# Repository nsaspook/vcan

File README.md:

# vcan

pic32mkmc Viision can motor tester

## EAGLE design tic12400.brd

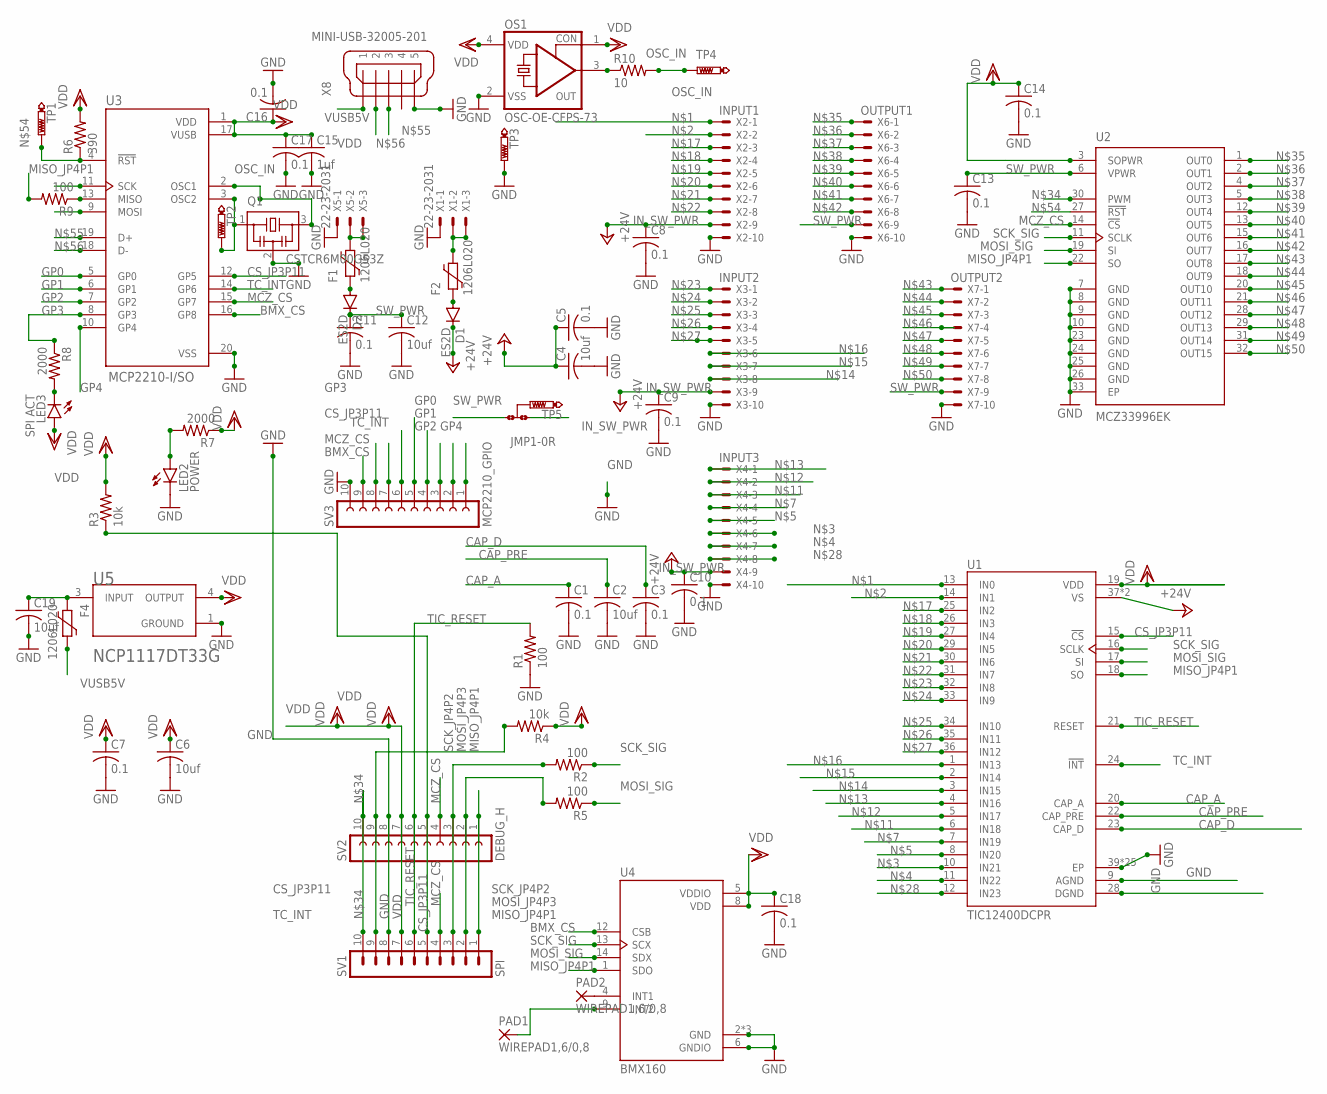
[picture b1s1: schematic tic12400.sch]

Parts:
C1, C3, C5, C7, C8, C9, C10, C11, C13, C14, C16, C17, C18: 0.1; C0805
C2, C4, C6, C12, C19: 10uf; C0805
C15: 1uf; C0805
D1, D2: ES2D; SMB
F1, F2, F4: 1206L020; 1206L
JMP1: +24_CONNECT; A0R-JMP
LED2: POWER; CHIP-LED0805
LED3: SPI ACT; CHIP-LED0805
OS1: OSC-OE-CFPS-73; 7.2X5.2-4-PAD
PAD1, PAD2: WIREPAD1,6/0,8; 1,6/0,8
Q1: CSTCR6M00G53Z; CSTCR6M
R1, R2, R5, R9: 100; R0805
R3, R4: 10k; R0805
R6: 390; R0805
R7, R8: 2000; R0805
R10: 10; R0805
SV1: SPI; MA10-1
SV2: DEBUG_H; FE10
SV3: MCP2210_GPIO; FE10
TP1, TP2, TP3, TP4, TP5: PTR1B1,27; B1,27
U1: TIC12400DCPR; SOP50P640X120-38N
U2: MCZ33996EK; SOP65P1030X265-33N
U3: MCP2210-I/SO; SOP65P780X200-20N
U4: BMX160; PQFN50P250X300X100-14N
U5: ON_SEMICONDUCTOR_NCP1117DT33GON_SEMICONDUCTOR_NCP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; ON_SEMICONDUCTOR_NCP1117DT33G_0
X1, X5: 22-23-2031
X2: INPUT1; KK-156-10
X3: INPUT2; KK-156-10
X4: INPUT3; KK-156-10
X6: OUTPUT1; KK-156-10
X7: OUTPUT2; KK-156-10
X8: MINI-USB-32005-201; 32005-201

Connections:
BMX_CS: SV3.9, U3.16 (GP8), U4.12 (CSB)
CAP_A: C1.1, U1.20 (CAP_A)
CAP_D: C3.1, U1.23 (CAP_D)
CAP_PRE: C2.1, U1.22 (CAP_PRE)
CS_JP3P11: R3.1, SV1.5, SV2.5, SV3.6, U1.15 (!CS), U3.12 (GP5)
GND: C1.2, C2.2, C3.2, C4.2, C5.2, C6.2, C7.2, C8.2, C9.2, C10.2, C11.2, C12.2, C13.2, C14.2, C15.2, C16.2, C17.2, C18.2, C19.2, LED2.C, OS1.2 (VSS), Q1.2, R1.1, SV1.8, SV2.8, SV3.10, TP3.TP, U1.9 (AGND), U1.28 (DGND), U1.39 (EP), U1.40 (EP), U1.41 (EP), U1.42 (EP), U1.43 (EP), U1.44 (EP), U1.45 (EP), U1.46 (EP), U1.47 (EP), U1.48 (EP), U1.49 (EP), U1.50 (EP), U1.51 (EP), U1.52 (EP), U1.53 (EP), U1.54 (EP), U1.55 (EP), U1.56 (EP), U1.57 (EP), U1.58 (EP), U1.59 (EP), U1.60 (EP), U1.61 (EP), U1.62 (EP), U1.63 (EP), U2.7 (GND), U2.8 (GND), U2.9 (GND), U2.10 (GND), U2.23 (GND), U2.24 (GND), U2.25 (GND), U2.26 (GND), U2.33 (EP), U3.20 (VSS), U4.2 (GND), U4.3 (GND), U4.6 (GNDIO), U4.7 (GND), U5.1 (GROUND), X1.1, X2.10, X3.10, X4.10, X5.1, X6.10, X7.10, X8.5; also elsewhere on the board
GP0: SV3.1, U3.5 (GP0)
GP1: SV3.2, U3.6 (GP1)
GP2: SV3.3, U3.7 (GP2)
GP3: R8.1, SV3.4, U3.8 (GP3)
GP4: SV3.5, U3.10 (GP4)
IN_SW_PWR: C4.1, C5.1, C8.1, C9.1, C10.1, D1.C, JMP1.3, U1.37 (VS), U1.38 (VS), X2.9, X3.9, X4.9
MCZ_CS: SV1.4, SV2.4, SV3.8, U2.14 (!CS), U3.15 (GP7)
MISO_JP4P1: R9.2, SV1.1, SV2.1, U1.18 (SO), U2.22 (SO), U4.1 (SDO)
MOSI_JP4P3: R5.2, SV1.2, SV2.2
MOSI_SIG: R5.1, U1.17 (SI), U2.19 (SI), U3.9 (MOSI), U4.14 (SDX)
unnamed: U1.13 (IN0), X2.1
unnamed: U1.14 (IN1), X2.2
unnamed: U1.10 (IN21), X4.6
unnamed: U1.11 (IN22), X4.7
unnamed: U1.8 (IN20), X4.5
unnamed: U1.7 (IN19), X4.4
unnamed: U1.6 (IN18), X4.3
unnamed: U1.5 (IN17), X4.2
unnamed: U1.4 (IN16), X4.1
unnamed: U1.3 (IN15), X3.8
unnamed: U1.2 (IN14), X3.7
unnamed: U1.1 (IN13), X3.6
unnamed: U1.25 (IN2), X2.3
unnamed: U1.26 (IN3), X2.4
unnamed: U1.27 (IN4), X2.5
unnamed: U1.29 (IN5), X2.6
unnamed: U1.30 (IN6), X2.7
unnamed: U1.31 (IN7), X2.8
unnamed: U1.32 (IN8), X3.1
unnamed: U1.33 (IN9), X3.2
unnamed: U1.34 (IN10), X3.3
unnamed: U1.35 (IN11), X3.4
unnamed: U1.36 (IN12), X3.5
unnamed: U1.12 (IN23), X4.8
unnamed: F2.1, X1.2, X1.3
unnamed: D2.A, F1.2
unnamed: F1.1, X5.2, X5.3
unnamed: SV1.10, SV2.10, U2.30 (PWM)
unnamed: U2.1 (OUT0), X6.1
unnamed: U2.2 (OUT1), X6.2
unnamed: U2.4 (OUT2), X6.3
unnamed: U2.5 (OUT3), X6.4
unnamed: U2.12 (OUT4), X6.5
unnamed: U2.13 (OUT5), X6.6
unnamed: U2.15 (OUT6), X6.7
unnamed: U2.16 (OUT7), X6.8
unnamed: U2.17 (OUT8), X7.1
unnamed: U2.18 (OUT9), X7.2
unnamed: U2.20 (OUT10), X7.3
unnamed: U2.21 (OUT11), X7.4
unnamed: U2.28 (OUT12), X7.5
unnamed: U2.29 (OUT13), X7.6
unnamed: U2.31 (OUT14), X7.7
unnamed: U2.32 (OUT15), X7.8
unnamed: D1.A, F2.2
unnamed: Q1.1, TP2.TP, U3.3 (OSC2)
unnamed: R6.1, TP1.TP, U2.27 (!RST), U3.4 (!RST)
unnamed: U3.19 (D+), X8.3
unnamed: U3.18 (D-), X8.2
unnamed: LED2.A, R7.2
unnamed: LED3.C, R8.2
unnamed: R9.1, U3.13 (MISO)
unnamed: OS1.3 (OUT), R10.1
unnamed: JMP1.2, TP5.TP
unnamed: PAD2.1, U4.4 (INT1)
unnamed: PAD1.1, U4.9 (INT2)
OSC_IN: Q1.3, R10.2, TP4.TP, U3.2 (OSC1)
SCK_JP4P2: R2.2, SV1.3, SV2.3
SCK_SIG: R2.1, U1.16 (SCLK), U2.11 (SCLK), U3.11 (SCK), U4.13 (SCX)
SW_PWR: C11.1, C12.1, C13.1, D2.C, JMP1.1, U2.6 (VPWR), X6.9, X7.9
TC_INT: R4.2, SV1.9, SV2.9, SV3.7, U1.24 (!INT), U3.14 (GP6)
TIC_RESET: R1.2, SV1.6, SV2.6, U1.21 (RESET)
USB5V_FUSE: C19.1, F4.2, U5.3 (INPUT); also elsewhere on the board
VDD: C6.1, C7.1, C14.1, C15.1, C16.1, C17.1, C18.1, LED3.A, OS1.1 (CON), OS1.4 (VDD), R3.2, R4.1, R6.2, R7.1, SV1.7, SV2.7, U1.19 (VDD), U2.3 (SOPWR), U3.1 (VDD), U3.17 (VUSB), U4.5 (VDDIO), U4.8 (VDD), U5.4 (OUTPUT); also elsewhere on the board
VUSB5V: F4.1, X8.1

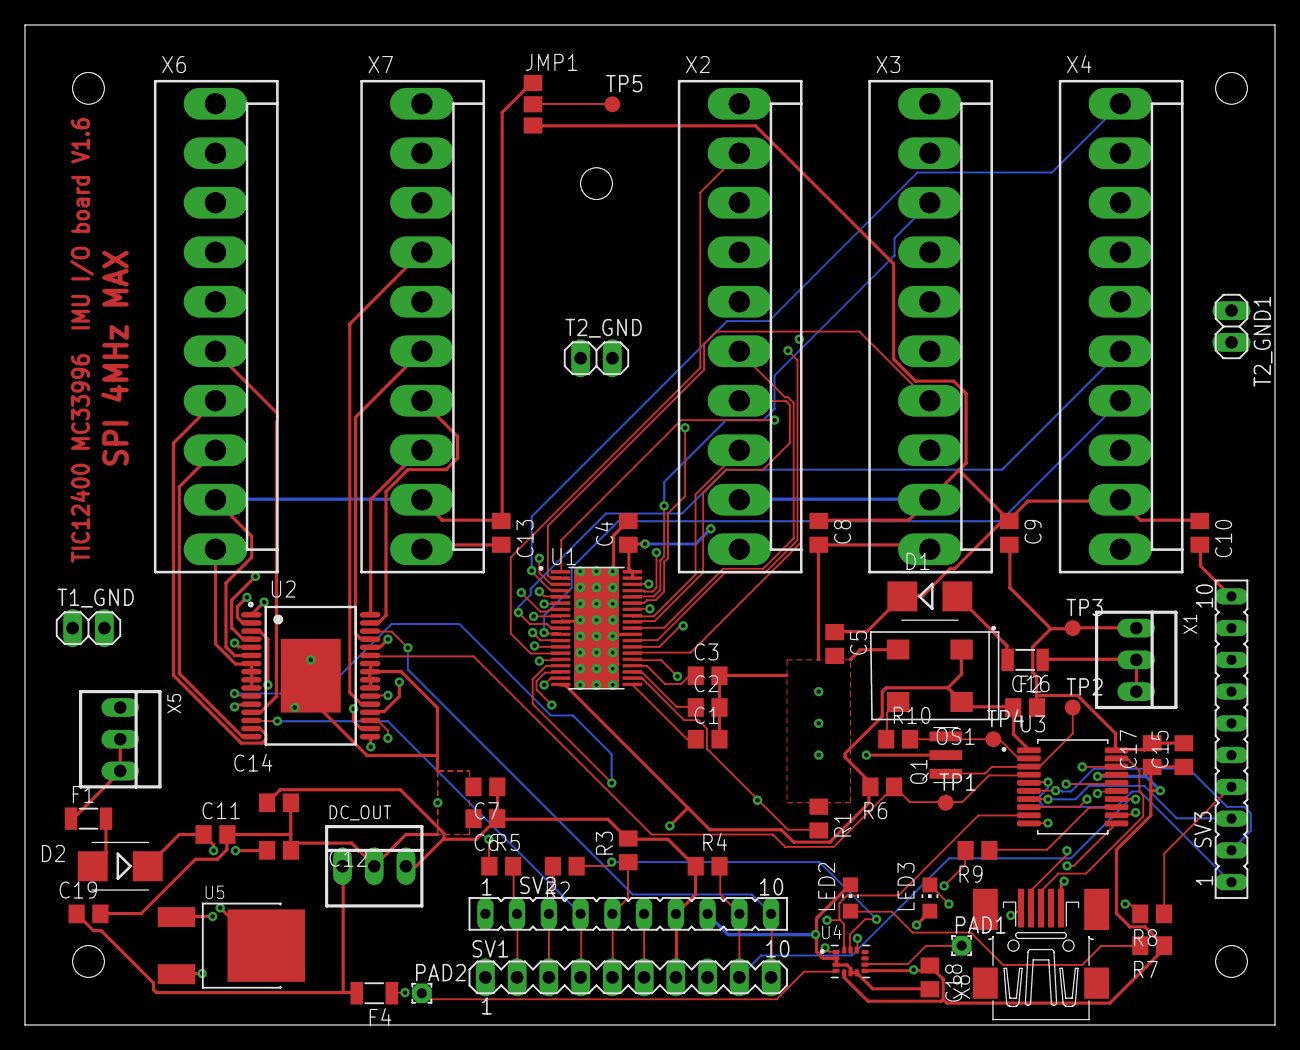
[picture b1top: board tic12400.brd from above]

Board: 4 copper layers, 100.0 x 80.0 mm, 66 parts (0 on the bottom side), 81 nets.

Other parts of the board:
DC_OUT: 22-23-2031
T1_GND, T2_GND, T2_GND1: gnd; 1X02

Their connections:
GND: DC_OUT.2, T1_GND.1, T1_GND.2, T2_GND.1, T2_GND.2, T2_GND1.1, T2_GND1.2; also elsewhere on the board
USB5V_FUSE: DC_OUT.1; also elsewhere on the board
VDD: DC_OUT.3; also elsewhere on the board

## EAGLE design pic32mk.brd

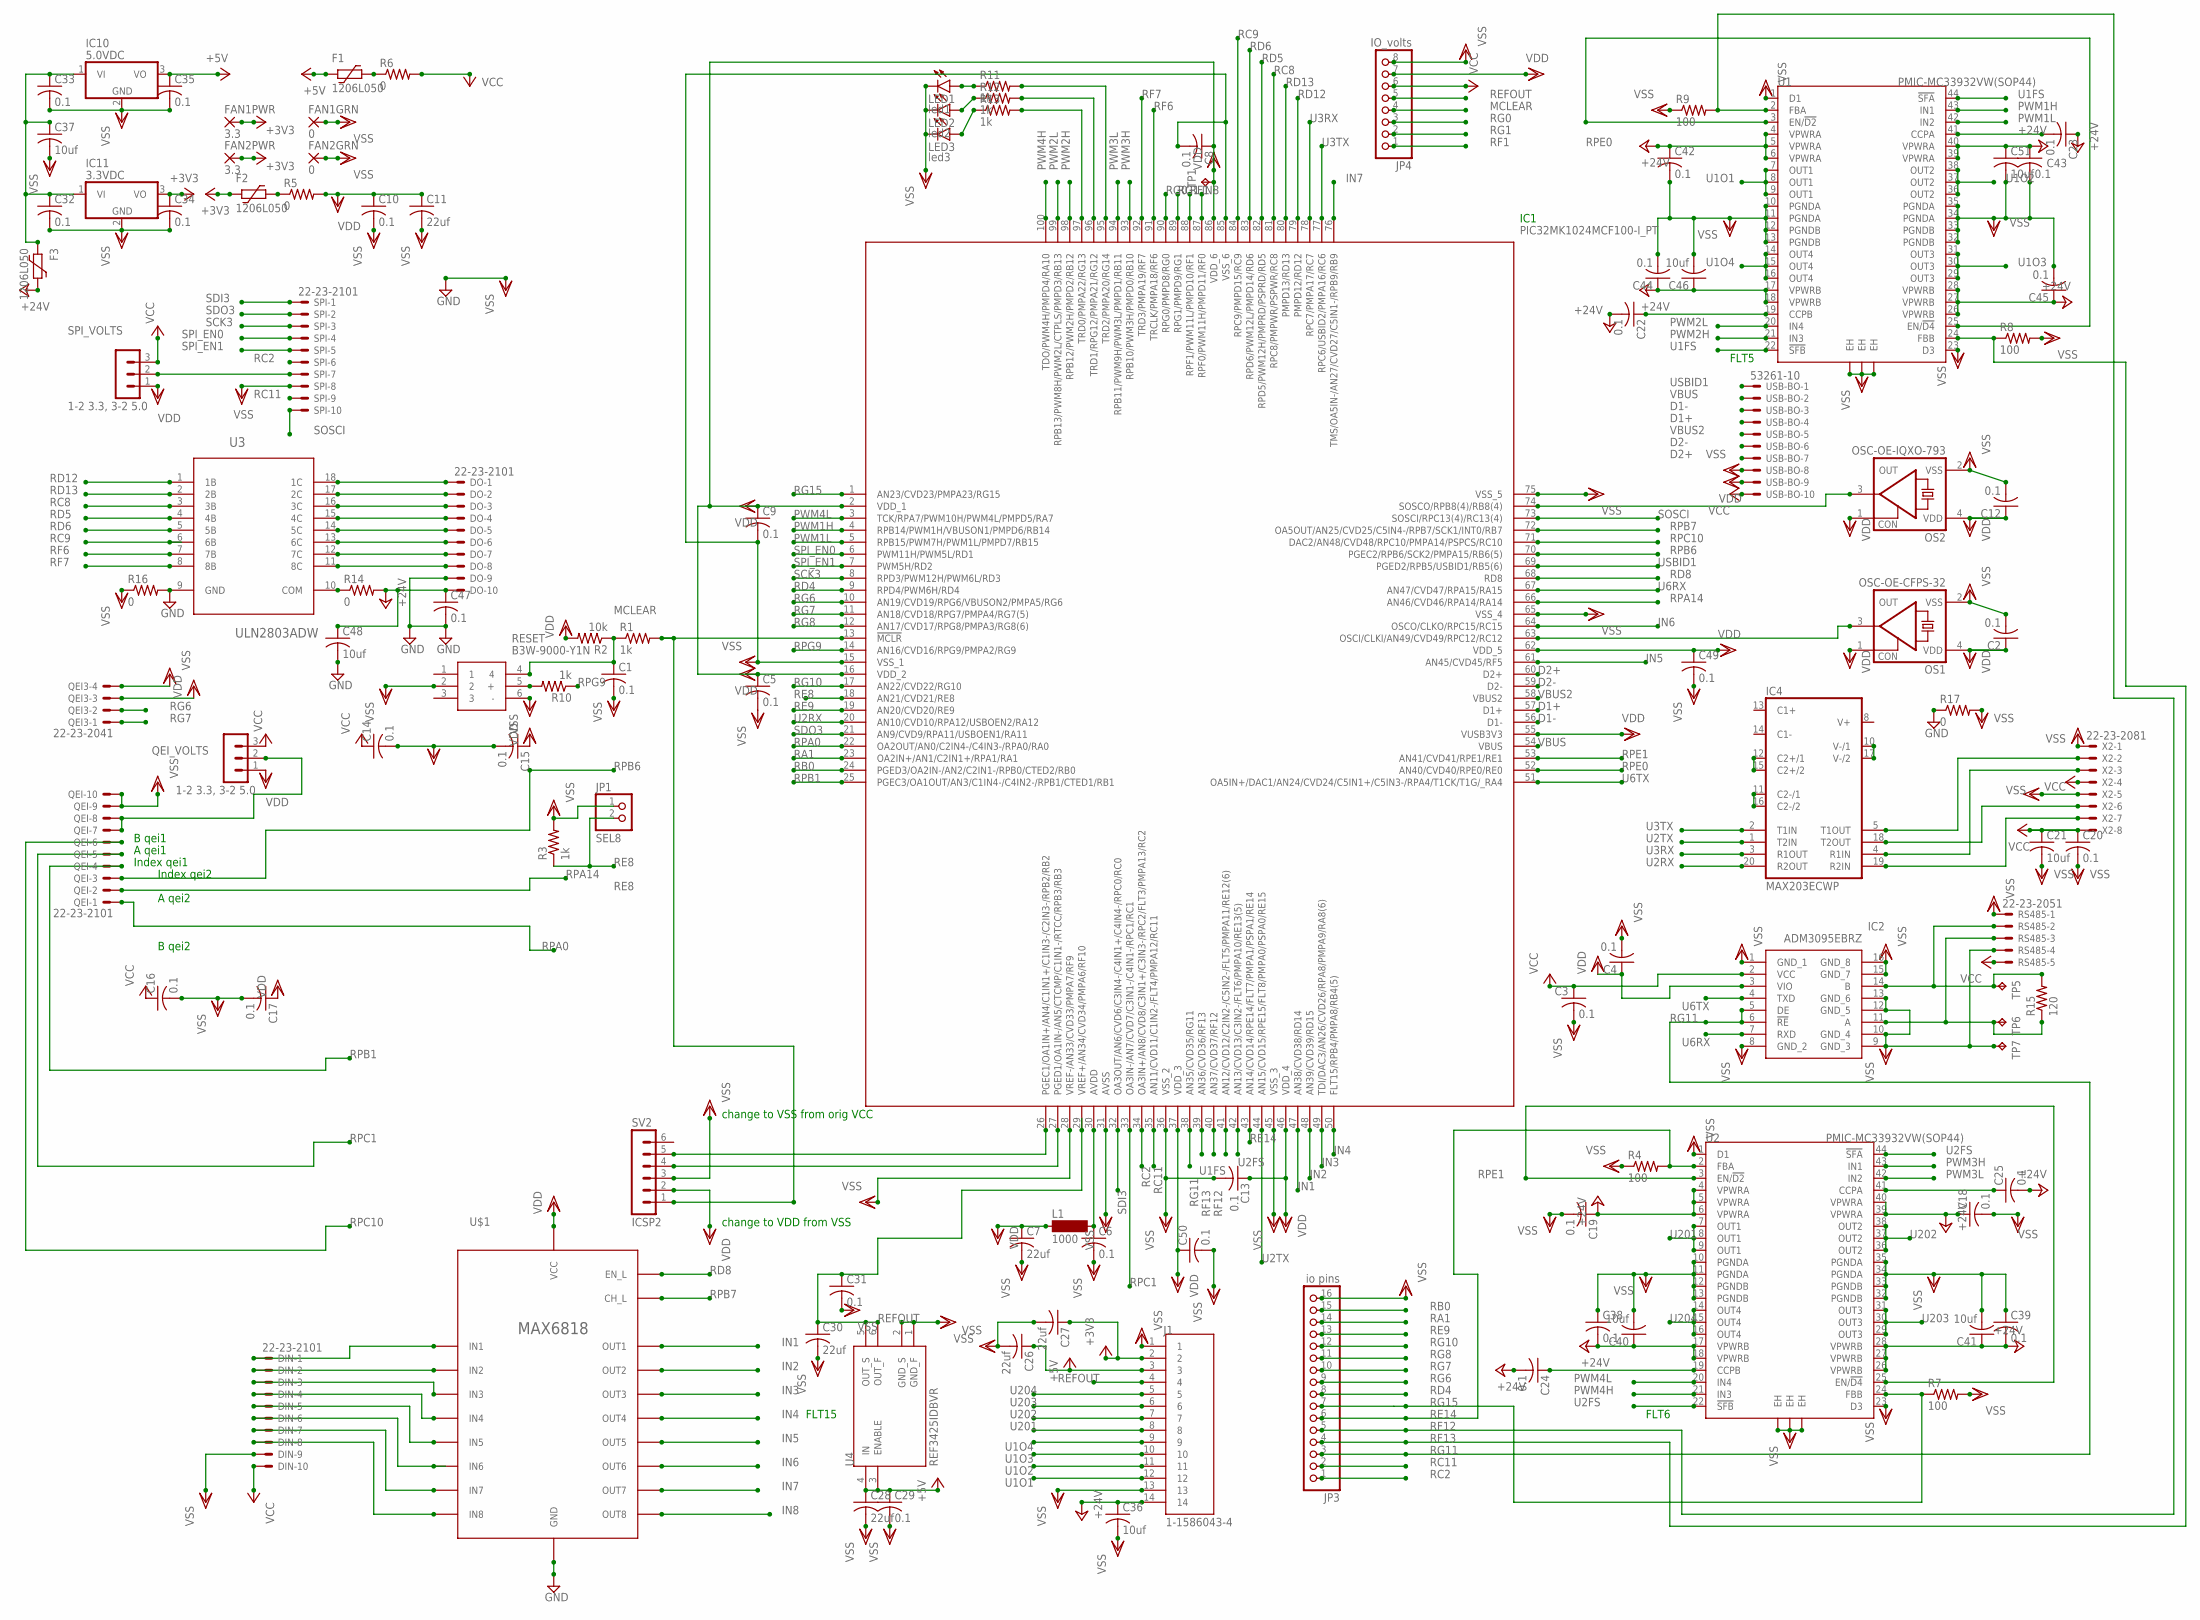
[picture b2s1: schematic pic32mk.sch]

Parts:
C1, C2, C3, C4, C5, C6, C8, C9, C10, C12, C13, C14, C15, C16, C17, C18, C19, C20, C22, C23, C24, C25, C29, C31, C32, C33, C34, C35, C38, C39, C42, C43, C44, C45, C47, C49, C50: 0.1; C0805
C7, C11, C26, C27, C28, C30: 22uf; C0805
C21, C36, C37, C40, C41, C46, C48, C51: 10uf; C1206
DIN: 22-23-2101
DO: 22-23-2101
F1, F2, F3: 1206L050; 1206L
FAN1GRN, FAN2GRN: 0; 1,6/0,8
FAN1PWR, FAN2PWR: 3.3; 1,6/0,8
IC1: PIC32MK1024MCF100-I_PT; QFP40P1400X1400X120-100N
IC2: ADM3095EBRZ; SOIC127P600X175-16N
IC4: MAX203ECWP; SO20L
IC10: 5.0VDC; TO220H
IC11: 3.3VDC; TO220H
J1: 1-1586043-4; TE_1-1586043-4
JP1: SEL8; 1X02
JP3: io pins; 1X16
JP4: IO_volts; 1X08
L1: 1000; SM-1206
LED1: led1; CHIPLED_1206
LED2: led2; CHIPLED_1206
LED3: led3; CHIPLED_1206
OS1: OSC-OE-CFPS-32; 7.2X5.2-4-PAD
OS2: OSC-OE-IQXO-793; 2.5X2-4-PAD
QEI: 22-23-2101
QEI3: 22-23-2041
QEI_VOLTS: 1-2 3.3, 3-2 5.0; MA03-1
R1, R3, R10, R11, R12, R13: 1k; M0805
R2: 10k; M0805
R4, R7, R8, R9: 100; R0805
R5, R6, R14, R16, R17: 0; M0805
R15: 120; R0805
RESET: B3W-9000-Y1N; B3W-9_1-LED
RS485: 22-23-2051
SPI: 22-23-2101
SPI_VOLTS: 1-2 3.3, 3-2 5.0; MA03-1
SV2: ICSP2; MA06-1
TP1, TP5, TP6, TP7: TPB1,27; B1,27
U1, U2: PMIC-MC33932VW(SOP44); SOP44-0.65-15.8X10.9MM
U3: ULN2803ADW; SOIC127P1030X265-18N
U4: REF3425IDBVR; SOT95P280X145-6N
U$1: MAX6818; SSOP20
USB-BO: 53261-10
X2: 22-23-2081

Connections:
+3V3: C27.1, C34.1, F2.2, FAN1PWR.1, FAN2PWR.1, IC11.3 (VO), J1.2
+5V: C26.1, C28.1, C29.1, C35.1, F1.2, IC10.3 (VO), J1.3, U4.3 (ENABLE), U4.4 (IN)
+24V: C18.1, C19.1, C22.2, C23.1, C24.2, C25.2, C36.1, C38.2, C39.2, C40.1, C41.1, C42.1, C43.1, C44.1, C45.1, C46.1, C47.1, C48.1, C51.1, DO.10, F3.1, J1.14, R14.2, U1.4 (VPWRA), U1.5 (VPWRA), U1.6 (VPWRA), U1.17 (VPWRB), U1.18 (VPWRB), U1.26 (VPWRB), U1.27 (VPWRB), U1.28 (VPWRB), U1.39 (VPWRA), U1.40 (VPWRA), U2.4 (VPWRA), U2.5 (VPWRA), U2.6 (VPWRA), U2.17 (VPWRB), U2.18 (VPWRB), U2.26 (VPWRB), U2.27 (VPWRB), U2.28 (VPWRB), U2.39 (VPWRA), U2.40 (VPWRA)
D1+: IC1.57 (D1+), USB-BO.4
D1-: IC1.56 (D1-), USB-BO.3
D2+: IC1.60 (D2+), USB-BO.7
D2-: IC1.59 (D2-), USB-BO.6
GND: C47.2, C48.2, DO.9, IC4.6 (GND), IC4.9 (GND), R16.2, R17.1, U3.9 (GND), U$1.GND
IN1: IC1.47 (AN38/CVD38/RD14), U$1.OUT1
IN2: IC1.48 (AN39/CVD39/RD15), U$1.OUT2
IN3: IC1.49 (TDI/DAC3/AN26/CVD26/RPA8/PMPA9/RA8(6)), U$1.OUT3
IN4: IC1.50 (FLT15/RPB4/PMPA8/RB4(5)), U$1.OUT4
IN5: IC1.61 (AN45/CVD45/RF5), U$1.OUT5
IN6: IC1.64 (OSCO/CLKO/RPC15/RC15), U$1.OUT6
IN7: IC1.76 (TMS/OA5IN-/AN27/CVD27/C5IN1-/RPB9/RB9), U$1.OUT7
IN8: IC1.87 (RPF0/PWM11H/PMPD11/RF0), U$1.OUT8
MCLEAR: C1.1, JP4.4, R1.1, R2.1, RESET.4; also elsewhere on the board
unnamed: IC1.74 (SOSCO/RPB8(4)/RB8(4)), OS2.3 (OUT)
unnamed: IC1.13 (!MCLR), R1.2, SV2.1
unnamed: F2.1, R5.1
unnamed: DIN.1, U$1.IN1
unnamed: C6.1, IC1.30 (AVDD), L1.2
unnamed: IC1.63 (OSCI/CLKI/AN49/CVD49/RPC12/RC12), OS1.3 (OUT)
unnamed: F1.1, R6.1
unnamed: IC1.27 (PGED1/OA1IN-/AN5/CTCMP/C1IN1-/RTCC/RPB3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), SV2.4
unnamed: IC1.26 (PGEC1/OA1IN+/AN4/C1IN1+/C1IN3-/C2IN3-/R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), SV2.5
unnamed: DIN.2, U$1.IN2
unnamed: DIN.3, U$1.IN3
unnamed: DIN.4, U$1.IN4
unnamed: DIN.5, U$1.IN5
unnamed: DIN.6, U$1.IN6
unnamed: DIN.7, U$1.IN7
unnamed: DIN.8, U$1.IN8
unnamed: C22.1, U1.19 (CCPB)
unnamed: C23.2, U1.41 (CCPA)
unnamed: C24.1, U2.19 (CCPB)
unnamed: C25.1, U2.41 (CCPA)
unnamed: QEI.7, QEI.8, QEI_VOLTS.2
unnamed: C32.1, C33.1, C37.1, F3.2, IC10.1 (VI), IC11.1 (VI)
unnamed: R10.2, RESET.5 (+)
unnamed: IC1.95 (TRD2/PMPA20/RG14), R11.2
unnamed: IC1.96 (TRD1/RPG12/PMPA21/RG12), R12.2
unnamed: IC1.97 (TRD0/PMPA22/RG13), R13.2
unnamed: LED1.A, R11.1
unnamed: LED2.A, R12.1
unnamed: LED3.A, R13.1
unnamed: IC2.14 (B), R15.2, RS485.2, TP5.TP
unnamed: IC2.11 (A), R15.1, RS485.3, TP6.TP
unnamed: IC4.10 (V-/1), IC4.17 (V-/2)
unnamed: IC4.11 (C2-/1), IC4.16 (C2-/2)
unnamed: IC4.12 (C2+/1), IC4.15 (C2+/2)
unnamed: IC4.5 (T1OUT), X2.2
unnamed: IC4.4 (R1IN), X2.3
unnamed: DO.1, U3.18 (1C)
unnamed: DO.2, U3.17 (2C)
unnamed: DO.3, U3.16 (3C)
unnamed: DO.4, U3.15 (4C)
unnamed: DO.5, U3.14 (5C)
unnamed: DO.6, U3.13 (6C)
unnamed: DO.7, U3.12 (7C)
unnamed: DO.8, U3.11 (8C)
unnamed: R14.1, U3.10 (COM)
unnamed: IC4.18 (T2OUT), X2.6
unnamed: IC4.19 (R2IN), X2.7
PWM1H: IC1.4 (RPB14/PWM1H/VBUSON1/PMPD6/RB14), U1.43 (IN1)
PWM1L: IC1.5 (RPB15/PWM7H/PWM1L/PMPD7/RB15), U1.42 (IN2)
PWM2H: IC1.98 (RPB12/PWM2H/PMPD2/RB12), U1.21 (IN3)
PWM2L: IC1.99 (RPB13/PWM8H/PWM2L/CTPLS/PMPD3/RB13), U1.20 (IN4)
PWM3H: IC1.93 (RPB10/PWM3H/PMPD0/RB10), U2.43 (IN1)
PWM3L: IC1.94 (RPB11/PWM9H/PWM3L/PMPD1/RB11), U2.42 (IN2)
PWM4H: IC1.100 (TDO/PWM4H/PMPD4/RA10), U2.21 (IN3)
PWM4L: IC1.3 (TCK/RPA7/PWM10H/PWM4L/PMPD5/RA7), U2.20 (IN4)
RA1: IC1.23 (OA2IN+/AN1/C2IN1+/RPA1/RA1), JP3.14
RB0: IC1.24 (PGED3/OA2IN-/AN2/C2IN1-/RPB0/CTED2/RB0), JP3.15
RC2: IC1.34 (OA3IN+/AN8/CVD8/C3IN1+/C3IN3-/RPC2/FLT3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), JP3.1, SPI.6
RC8: IC1.81 (RPC8/PMPWR/PSPWR/RC8), U3.3 (3B)
RC9: IC1.84 (RPC9/PMPD15/RC9), U3.6 (6B)
RC11: IC1.35 (AN11/CVD11/C1IN2-/FLT4/PMPA12/RC11), JP3.2, SPI.9
RD4: IC1.9 (RPD4/PWM6H/RD4), JP3.8
RD5: IC1.82 (RPD5/PWM12H/PMPRD/PSPRD/RD5), U3.4 (4B)
RD6: IC1.83 (RPD6/PWM12L/PMPD14/RD6), U3.5 (5B)
RD8: IC1.68 (RD8), U$1.EN_L
RD12: IC1.79 (PMPD12/RD12), U3.1 (1B)
RD13: IC1.80 (PMPD13/RD13), U3.2 (2B)
RE8: IC1.18 (AN21/CVD21/RE8), JP1.2, R3.1
RE9: IC1.19 (AN20/CVD20/RE9), JP3.13
RE14: IC1.43 (AN14/CVD14/RPE14/FLT7/PMPA1/PSPA1/RE14), JP3.6, R4.2, U2.2 (FBA)
REFOUT: C30.1, C31.1, IC1.29 (VREF+/AN34/CVD34/PMPA6/RF10), J1.4, JP4.5, U4.5 (OUT_S), U4.6 (OUT_F); also elsewhere on the board
RF1: IC1.88 (RPF1/PWM11L/PMPD10/RF1), JP4.1
RF6: IC1.91 (TRCLK/PMPA18/RF6), U3.7 (7B)
RF7: IC1.92 (TRD3/PMPA19/RF7), U3.8 (8B)
RF12: IC1.40 (AN37/CVD37/RF12), JP3.5, R9.2, U1.2 (FBA)
RF13: IC1.39 (AN36/CVD36/RF13), JP3.4, R8.1, U1.24 (FBB)
RG0: IC1.90 (RPG0/PMPD8/RG0), JP4.3
RG1: IC1.89 (RPG1/PMPD9/RG1), JP4.2
RG6: IC1.10 (AN19/CVD19/RPG6/VBUSON2/PMPA5/RG6), JP3.9, QEI3.2
RG7: IC1.11 (AN18/CVD18/RPG7/PMPA4/RG7(5)), JP3.10, QEI3.1
RG8: IC1.12 (AN17/CVD17/RPG8/PMPA3/RG8(6)), JP3.11
RG10: IC1.17 (AN22/CVD22/RG10), JP3.12
RG11: IC1.38 (AN35/CVD35/RG11), IC2.5 (DE), IC2.6 (!RE), JP3.3
RG15: IC1.1 (AN23/CVD23/PMPA23/RG15), JP3.7, R7.1, U2.24 (FBB)
RPA0: IC1.22 (OA2OUT/AN0/C2IN4-/C4IN3-/RPA0/RA0), QEI.1
RPA14: IC1.66 (AN46/CVD46/RPA14/RA14), QEI.2
RPB1: IC1.25 (PGEC3/OA1OUT/AN3/C1IN4-/C4IN2-/RPB1/CTE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), QEI.4
RPB6: IC1.70 (PGEC2/RPB6/SCK2/PMPA15/RB6(5)), QEI.3
RPB7: IC1.72 (OA5OUT/AN25/CVD25/C5IN4-/RPB7/SCK1/INT0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), U$1.CH_L
RPC1: IC1.33 (OA3IN-/AN7/CVD7/C3IN1-/C4IN1-/RPC1/RC1), QEI.5
RPC10: IC1.71 (DAC2/AN48/CVD48/RPC10/PMPA14/PSPCS/RC10), QEI.6
RPE0: IC1.52 (AN40/CVD40/RPE0/RE0), U1.3 (EN/!D2), U1.25 (EN/!D4)
RPE1: IC1.53 (AN41/CVD41/RPE1/RE1), U2.3 (EN/!D2), U2.25 (EN/!D4)
RPG9: IC1.14 (AN16/CVD16/RPG9/PMPA2/RG9), R10.1
SCK3: IC1.8 (RPD3/PWM12H/PWM6L/RD3), SPI.3
SDI3: IC1.32 (OA3OUT/AN6/CVD6/C3IN4-/C4IN1+/C4IN4-/RP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), SPI.1
SDO3: IC1.21 (AN9/CVD9/RPA11/USBOEN1/RA11), SPI.2
SOSCI: IC1.73 (SOSCI/RPC13(4)/RC13(4)), SPI.10
SPIVOLTS: SPI.7, SPI_VOLTS.2
SPI_EN0: IC1.6 (PWM11H/PWM5L/RD1), SPI.4
SPI_EN1: IC1.7 (PWM5H/RD2), SPI.5
U1FS: IC1.41 (AN12/CVD12/C2IN2-/C5IN2-/FLT5/PMPA11/RE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), U1.22 (!SFB), U1.44 (!SFA)
U1O1: J1.12, U1.7 (OUT1), U1.8 (OUT1), U1.9 (OUT1)
U1O2: J1.11, U1.36 (OUT2), U1.37 (OUT2), U1.38 (OUT2)
U1O3: J1.10, U1.29 (OUT3), U1.30 (OUT3), U1.31 (OUT3)
U1O4: J1.9, U1.14 (OUT4), U1.15 (OUT4), U1.16 (OUT4)
U2FS: IC1.42 (AN13/CVD13/C3IN2-/FLT6/PMPA10/RE13(5)), U2.22 (!SFB), U2.44 (!SFA)
U2RX: IC1.20 (AN10/CVD10/RPA12/USBOEN2/RA12), IC4.20 (R2OUT)
U2TX: IC1.44 (AN15/CVD15/RPE15/FLT8/PMPA0/PSPA0/RE15), IC4.1 (T2IN)
U3RX: IC1.78 (RPC7/PMPA17/RC7), IC4.3 (R1OUT)
U3TX: IC1.77 (RPC6/USBID2/PMPA16/RC6), IC4.2 (T1IN)
U6RX: IC1.67 (AN47/CVD47/RPA15/RA15), IC2.7 (RXD)
U6TX: IC1.51 (OA5IN+/DAC1/AN24/CVD24/C5IN1+/C5IN3-/RP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), IC2.4 (TXD)
U201: J1.8, U2.7 (OUT1), U2.8 (OUT1), U2.9 (OUT1)
U202: J1.7, U2.36 (OUT2), U2.37 (OUT2), U2.38 (OUT2)
U203: J1.6, U2.29 (OUT3), U2.30 (OUT3), U2.31 (OUT3)
U204: J1.5, U2.14 (OUT4), U2.15 (OUT4), U2.16 (OUT4)
USBID1: IC1.69 (PGED2/RPB5/USBID1/RB5(6)), USB-BO.1
VBUS: IC1.54 (VBUS), USB-BO.2
VBUS2: IC1.58 (VBUS2), USB-BO.5
VCC: C3.1, C14.1, C16.1, C20.1, C21.1, DIN.10, IC2.2 (VCC), IC4.7 (VCC), JP4.6, QEI_VOLTS.3, R6.2, RS485.5, SPI_VOLTS.3, USB-BO.10, X2.4, X2.8
VDD: C2.1, C4.1, C5.1, C7.1, C8.1, C9.1, C10.1, C11.1, C12.1, C13.1, C15.1, C17.1, C49.1, C50.1, IC1.2 (VDD_1), IC1.16 (VDD_2), IC1.37 (VDD_3), IC1.46 (VDD_4), IC1.55 (VUSB3V3), IC1.62 (VDD_5), IC1.86 (VDD_6), IC2.3 (VIO), JP4.7, L1.1, OS1.1 (CON), OS1.4 (VDD), OS2.1 (CON), OS2.4 (VDD), QEI3.3, QEI_VOLTS.1, R2.2, R5.2, SPI_VOLTS.1, SV2.2, TP1.TP, U$1.VCC, USB-BO.9
VSS: C1.2, C2.2, C3.2, C4.2, C5.2, C6.2, C7.2, C8.2, C9.2, C10.2, C11.2, C12.2, C13.2, C14.2, C15.2, C16.2, C17.2, C18.2, C19.2, C20.2, C21.2, C26.2, C27.2, C28.2, C29.2, C30.2, C31.2, C32.2, C33.2, C34.2, C35.2, C36.2, C37.2, C38.1, C39.1, C40.2, C41.2, C42.2, C43.2, C44.2, C45.2, C46.2, C49.2, C50.2, C51.2, DIN.9, FAN1GRN.1, FAN2GRN.1, IC1.15 (VSS_1), IC1.28 (VREF-/AN33/CVD33/PMPA7/RF9), IC1.31 (AVSS), IC1.36 (VSS_2), IC1.45 (VSS_3), IC1.65 (VSS_4), IC1.75 (VSS_5), IC1.85 (VSS_6), IC2.1 (GND_1), IC2.8 (GND_2), IC2.9 (GND_3), IC2.10 (GND_4), IC2.12 (GND_5), IC2.13 (GND_6), IC2.15 (GND_7), IC2.16 (GND_8), IC10.2 (GND), IC11.2 (GND), J1.1, J1.13, JP1.1, JP3.16, JP4.8, LED1.C, LED2.C, LED3.C, OS1.2 (VSS), OS2.2 (VSS), QEI.9, QEI.10, QEI3.4, R3.2, R4.1, R7.2, R8.2, R9.1, R16.1, R17.2, RESET.2, RESET.6 (-), RS485.1, RS485.4, SPI.8, SV2.3, TP7.TP, U1.1 (D1), U1.10 (PGNDA), U1.11 (PGNDA), U1.12 (PGNDB), U1.13 (PGNDB), U1.23 (D3), U1.32 (PGNDB), U1.33 (PGNDB), U1.34 (PGNDA), U1.35 (PGNDA), U1.EH@1 (EH), U1.EH@2 (EH), U1.EH@3 (EH), U2.1 (D1), U2.10 (PGNDA), U2.11 (PGNDA), U2.12 (PGNDB), U2.13 (PGNDB), U2.23 (D3), U2.32 (PGNDB), U2.33 (PGNDB), U2.34 (PGNDA), U2.35 (PGNDA), U2.EH@1 (EH), U2.EH@2 (EH), U2.EH@3 (EH), U4.1 (GND_F), U4.2 (GND_S), USB-BO.8, X2.1, X2.5; also elsewhere on the board

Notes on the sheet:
change to VDD from VSS
change to VSS from orig VCC
A qei2
B qei2
Index qei2
Index qei1
A qei1
B qei1
FLT6
FLT5
FLT15

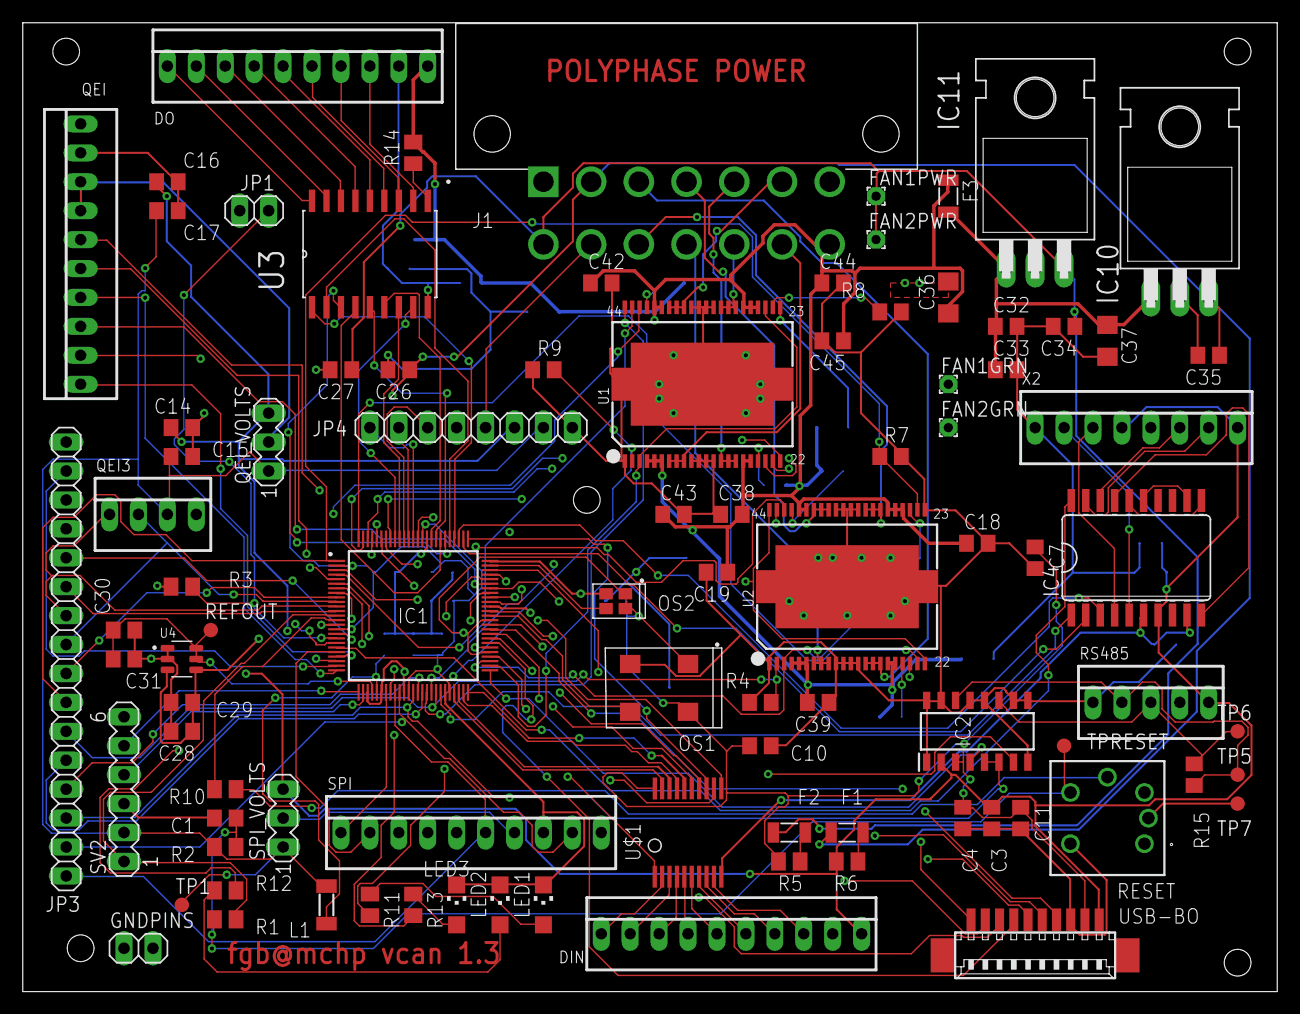
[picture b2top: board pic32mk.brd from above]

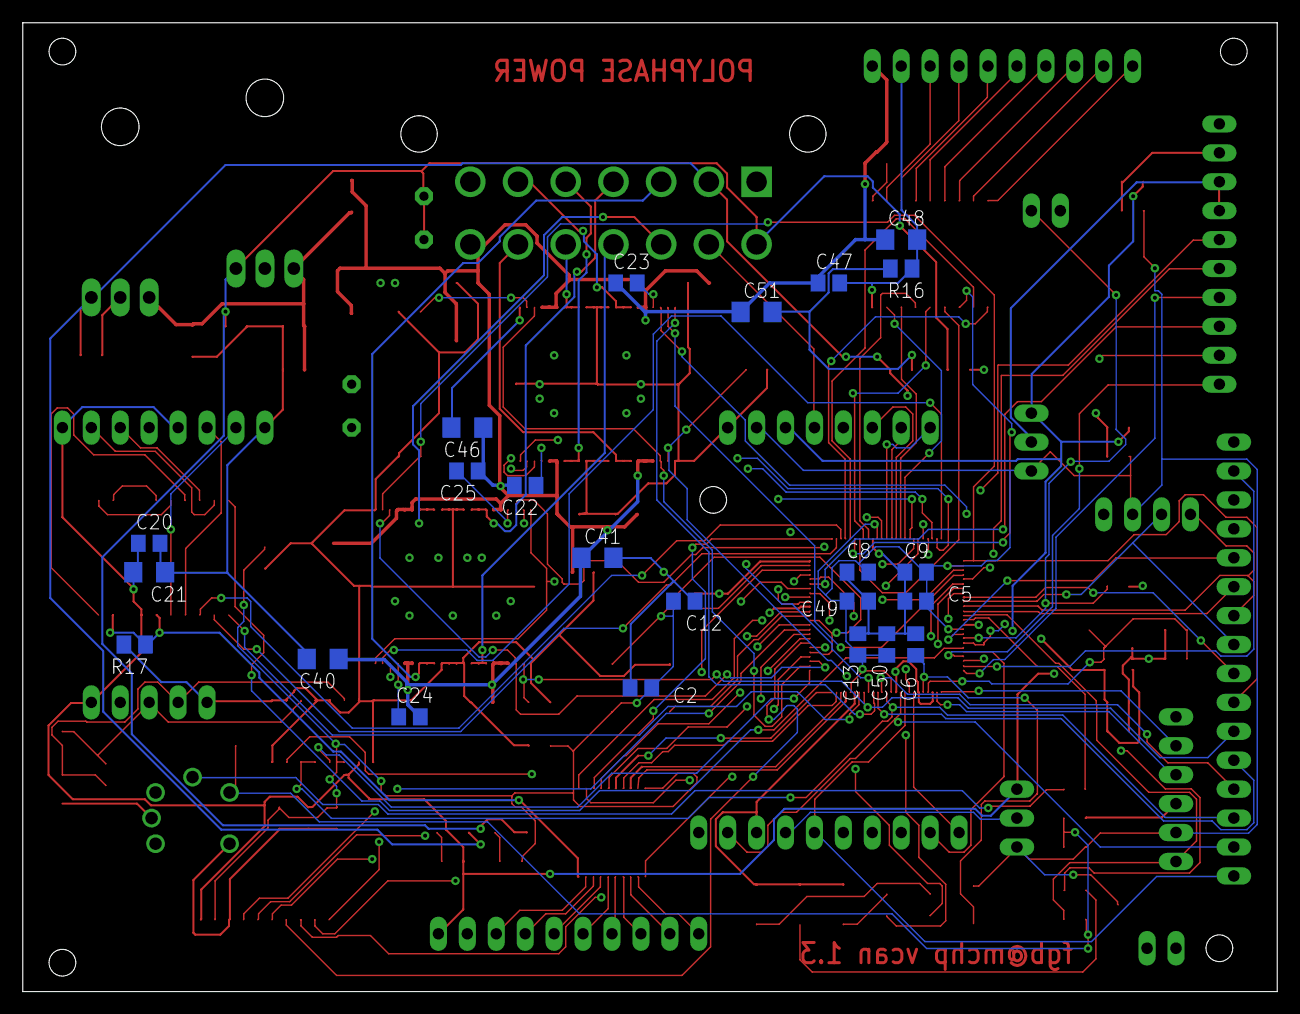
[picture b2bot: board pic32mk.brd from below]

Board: 4 copper layers, 110.2 x 85.1 mm, 114 parts (23 on the bottom side), 140 nets.

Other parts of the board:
GNDPINS: 0; 1X02
REFOUT: TPB1,27; B1,27
TPRESET: TPB1,27; B1,27

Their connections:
MCLEAR: TPRESET.TP; also elsewhere on the board
REFOUT: REFOUT.TP; also elsewhere on the board
VSS: GNDPINS.1, GNDPINS.2; also elsewhere on the board

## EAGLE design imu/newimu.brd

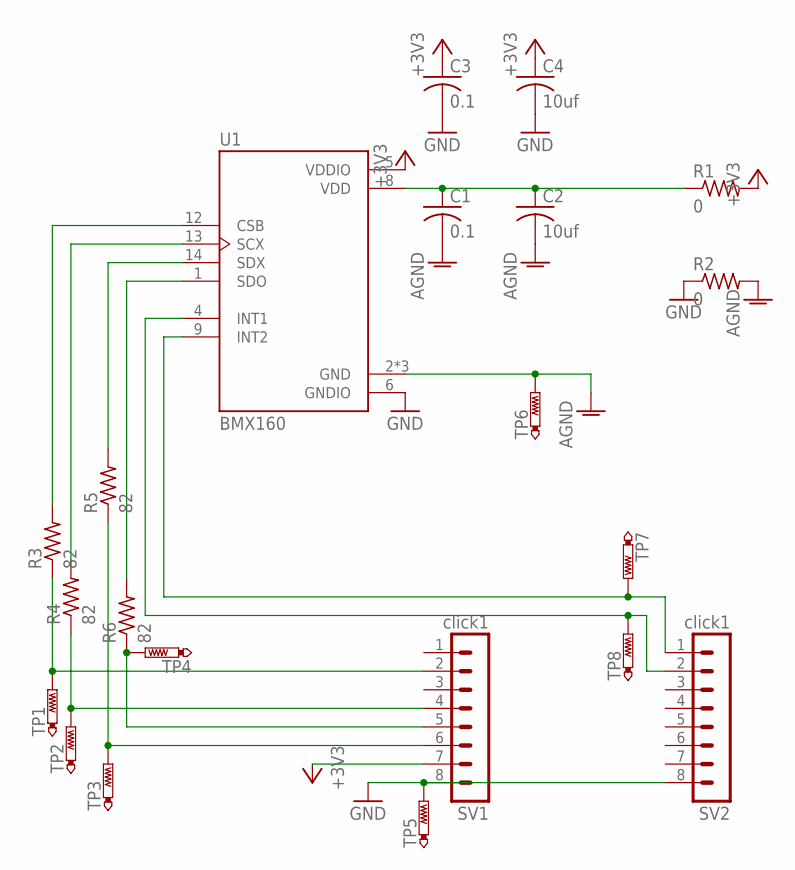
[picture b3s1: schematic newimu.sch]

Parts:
C1, C3: 0.1; C0805
C2, C4: 10uf; C0805
R1, R2: 0; M0805
R3, R4, R5, R6: 82; M0805
SV1, SV2: click1; MA08-1
TP1, TP2, TP3, TP4, TP5, TP6, TP7, TP8: PTR1B1,27; B1,27
U1: BMX160; PQFN50P250X300X100-14N

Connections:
+3V3: C3.1, C4.1, R1.2, SV1.7, U1.5 (VDDIO)
AGND: C1.2, C2.2, R2.2, TP6.TP, U1.2 (GND), U1.3 (GND), U1.7 (GND)
GND: C3.2, C4.2, R2.1, SV1.8, SV2.8, TP5.TP, U1.6 (GNDIO)
unnamed: R4.2, U1.13 (SCX)
unnamed: SV2.1, TP7.TP, U1.9 (INT2)
unnamed: SV2.2, TP8.TP, U1.4 (INT1)
unnamed: R6.2, U1.1 (SDO)
unnamed: R5.1, SV1.6, TP3.TP
unnamed: R3.1, SV1.2, TP1.TP
unnamed: C1.1, C2.1, R1.1, U1.8 (VDD)
unnamed: R3.2, U1.12 (CSB)
unnamed: R4.1, SV1.4, TP2.TP
unnamed: R5.2, U1.14 (SDX)
unnamed: R6.1, SV1.5, TP4.TP

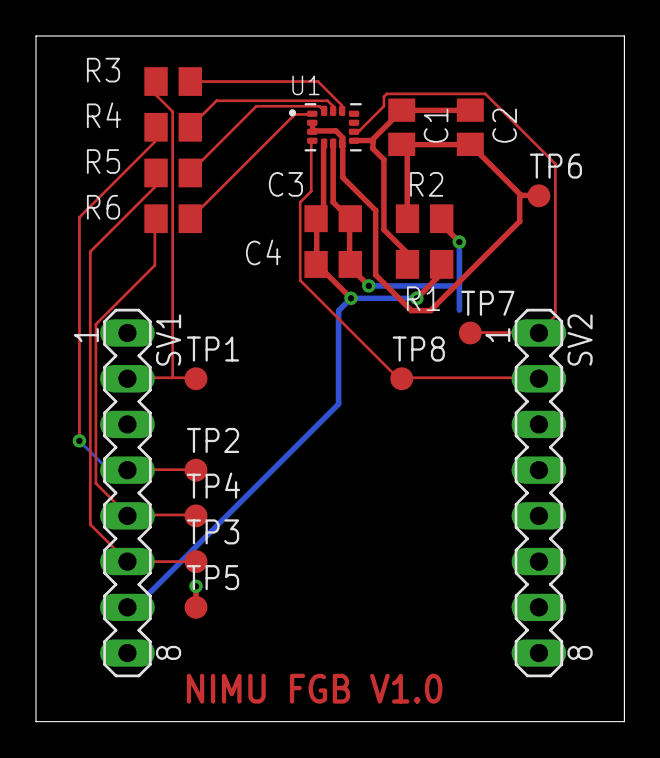
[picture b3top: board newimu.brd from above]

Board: 2 copper layers, 32.7 x 38.1 mm, 21 parts (0 on the bottom side), 14 nets.

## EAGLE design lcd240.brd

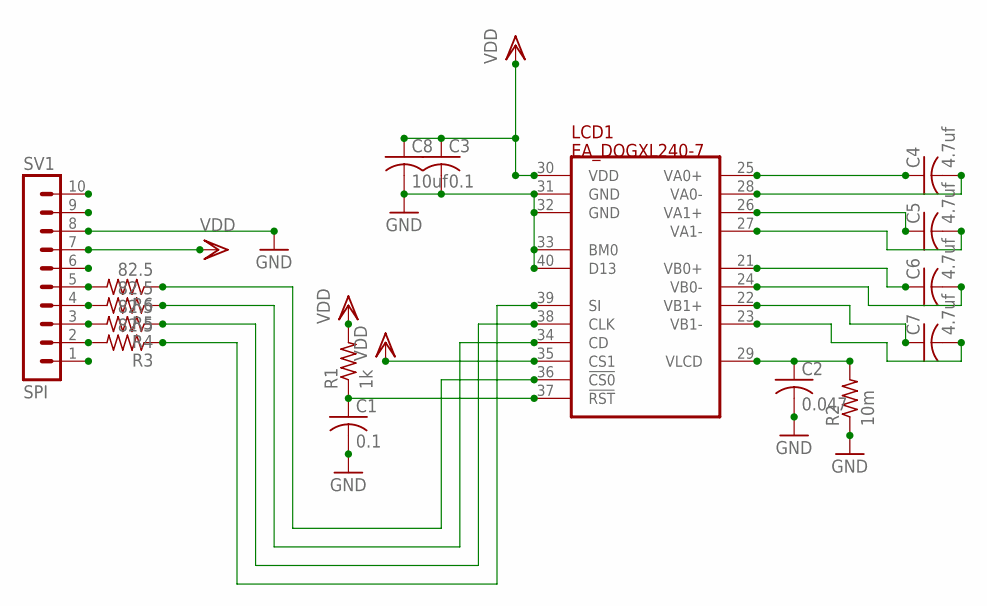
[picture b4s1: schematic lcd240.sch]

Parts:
C1, C3: 0.1; C1206
C2: 0.047; C1206
C4, C5, C6, C7: 4.7uf; C1206
C8: 10uf; C1206
LCD1: EA_DOGXL240-7
R1: 1k; R0805
R2: 10m; R0805
R3, R4, R5, R6: 82.5; R0805
SV1: SPI; MA10-1

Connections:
GND: C1.2, C2.2, C3.2, C8.2, LCD1.31 (GND), LCD1.32 (GND), LCD1.33 (BM0), LCD1.40 (D13), R2.1, SV1.8
unnamed: C4.2, LCD1.28 (VA0-)
unnamed: C5.1, LCD1.26 (VA1+)
unnamed: C2.1, LCD1.29 (VLCD), R2.2
unnamed: C1.1, LCD1.37 (!RST!), R1.1
unnamed: C5.2, LCD1.27 (VA1-)
unnamed: C4.1, LCD1.25 (VA0+)
unnamed: C6.1, LCD1.21 (VB0+)
unnamed: C6.2, LCD1.24 (VB0-)
unnamed: C7.1, LCD1.22 (VB1+)
unnamed: C7.2, LCD1.23 (VB1-)
unnamed: LCD1.36 (!CS0!), R6.1
unnamed: LCD1.34 (CD), R5.1
unnamed: LCD1.38 (CLK), R4.1
unnamed: LCD1.39 (SI), R3.1
unnamed: R3.2, SV1.2
unnamed: R4.2, SV1.3
unnamed: R6.2, SV1.5
unnamed: R5.2, SV1.4
VDD: C3.1, C8.1, LCD1.30 (VDD), LCD1.35 (CS1), R1.2, SV1.7

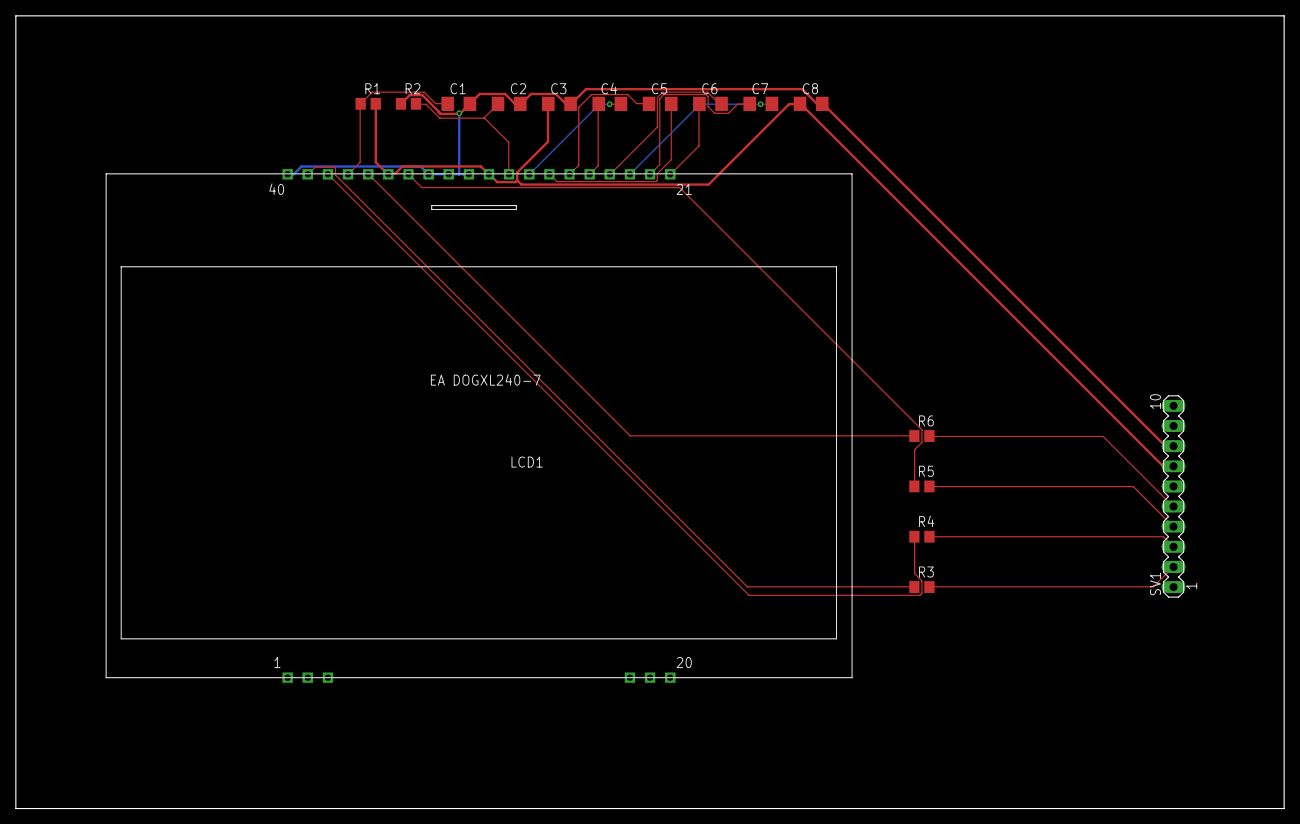
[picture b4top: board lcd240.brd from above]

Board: 2 copper layers, 160.0 x 100.0 mm, 16 parts (0 on the bottom side), 20 nets.

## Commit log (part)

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2020-09-17 add MX2 code for archive
2020-10-18 add IMU code for MCJ board
2021-10-22 up:wq
2024-11-10 update SLC3300 driver
